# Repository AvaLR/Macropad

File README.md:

# Macropad

PCB:
- Started to design this in KiCad starting with the skematic design and then moving to the PCB design.
- I originally started with a 3X4 with 2 rotary encoders and 1 OLED
- I wanted to add LEDs so I removed 1 rotary encoder and made the other rotary encoder's button the same as button 3. Also made it a 3X3 instead of a 3X4.
- Wiring was a challenge and reminded me of that Flow Free game so it was kinda fun in that aspect.

Enclosure:
- A lot easier then the PCB
- First I inserted a .step file of my PCB into AutoDesk Fusion 
- Then based on the PCB I made my bottom enclosure (120mm X 100mm X 13mm) with 2.9mm holes in each corner so I can add screws to put my top and bottom enclosures together. I also put a hole on back for the USB.
- After I made the bottom enclosure I created the top enclosure with holes for all my buttons (inserting my PCB design really helped for this part because I knew exactly where the holes went). I put 2.9mm holes here as well to again be able to put the top and bottom together. 
- The top enclosure was a 120mm x 100mm x 3mm so with the top and bottom enclosure together it turned into a 120mm x 100mm x 16mm enclosure.

Firmware:
- Created 3 layers of Buttons: Daily, AVTF & Coding
- Each layer does different things that will make my life easier from study time to coding to editing videos!
- Each layer has its own RGB unkeyglow color, and the OLED will show what the layer I'm on

Credit: 
- Info & Guide - Hack Club
- PCB, Enclosure, Firmware - Ava Russell using QMK Resources/Code/Guide
- Debugging Help - AI

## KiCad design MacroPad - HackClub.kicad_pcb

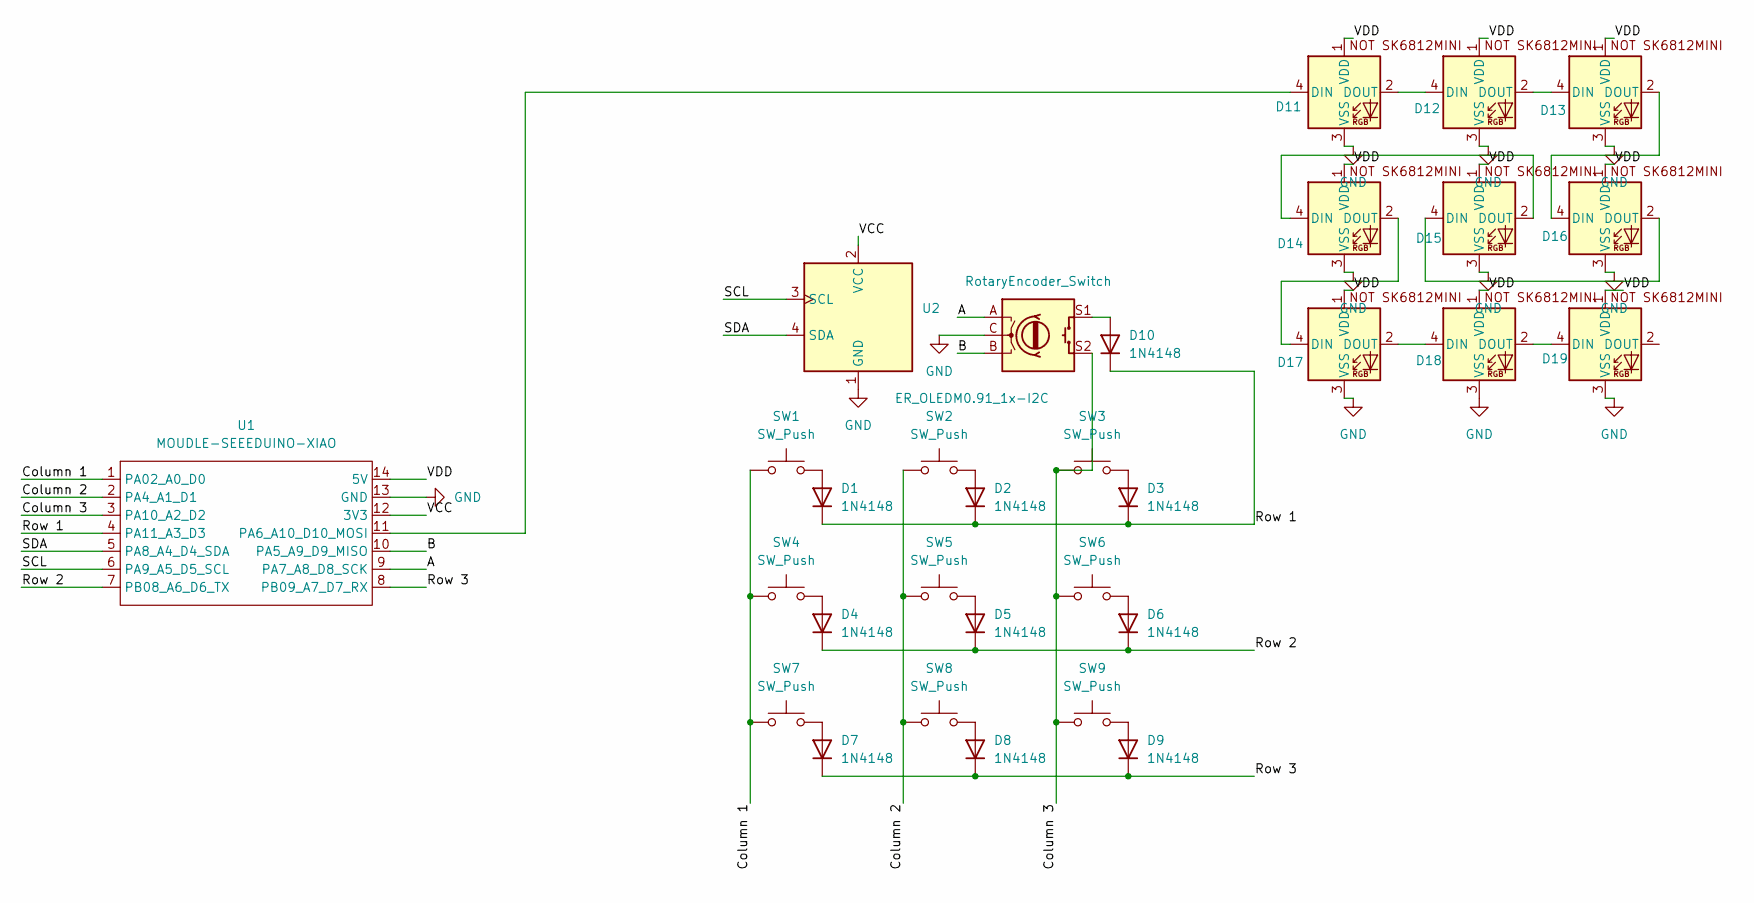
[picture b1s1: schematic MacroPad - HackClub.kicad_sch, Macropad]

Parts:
D1, D2, D3, D4, D5, D6, D7, D8, D9, D10: 1N4148; D_DO-35_SOD27_P7.62mm_Horizontal
D11, D12, D13, D14, D15, D16, D17, D18, D19: SK6812MINI-E; SK6812MINI-E_fixed
SW1, SW2, SW3, SW4, SW5, SW6, SW7, SW8, SW9: SW_Push; SW_Cherry_MX_1.00u_PCB
SW10: RotaryEncoder_Switch; RotaryEncoder_Alps_EC11E-Switch_Vertical_H20mm
U1: MOUDLE-SEEEDUINO-XIAO; XIAO-Generic-Hybrid-14P-2.54-21X17.8MM
U2: ER_OLEDM0.91_1x-I2C

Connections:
/A: SW10.A, U1.9 (PA7_A8_D8_SCK)
/B: SW10.B, U1.10 (PA5_A9_D9_MISO)
/Column 1: SW1.1, SW4.1, SW7.1, U1.1 (PA02_A0_D0)
/Column 2: SW2.1, SW5.1, SW8.1, U1.2 (PA4_A1_D1)
/Column 3: SW3.1, SW6.1, SW9.1, SW10.S2, U1.3 (PA10_A2_D2)
/Row 1: D1.1 (K), D2.1 (K), D3.1 (K), D10.1 (K), U1.4 (PA11_A3_D3)
/Row 2: D4.1 (K), D5.1 (K), D6.1 (K), U1.7 (PB08_A6_D6_TX)
/Row 3: D7.1 (K), D8.1 (K), D9.1 (K), U1.8 (PB09_A7_D7_RX)
/SCL: U1.6 (PA9_A5_D5_SCL), U2.3 (SCL)
/SDA: U1.5 (PA8_A4_D4_SDA), U2.4 (SDA)
/VCC: U1.12 (3V3), U2.2 (VCC)
/VDD: D11.1 (VDD), D12.1 (VDD), D13.1 (VDD), D14.1 (VDD), D15.1 (VDD), D16.1 (VDD), D17.1 (VDD), D18.1 (VDD), D19.1 (VDD), U1.14 (5V)
GND: D11.3 (VSS), D12.3 (VSS), D13.3 (VSS), D14.3 (VSS), D15.3 (VSS), D16.3 (VSS), D17.3 (VSS), D18.3 (VSS), D19.3 (VSS), SW10.C, U1.13 (GND), U2.1 (GND)
unnamed: D1.2 (A), SW1.2
unnamed: D2.2 (A), SW2.2
unnamed: D3.2 (A), SW3.2
unnamed: D4.2 (A), SW4.2
unnamed: D5.2 (A), SW5.2
unnamed: D6.2 (A), SW6.2
unnamed: D7.2 (A), SW7.2
unnamed: D8.2 (A), SW8.2
unnamed: D9.2 (A), SW9.2
unnamed: D10.2 (A), SW10.S1
unnamed: D11.4 (DIN), U1.11 (PA6_A10_D10_MOSI)
unnamed: D11.2 (DOUT), D12.4 (DIN)
unnamed: D12.2 (DOUT), D13.4 (DIN)
unnamed: D13.2 (DOUT), D16.4 (DIN)
unnamed: D14.4 (DIN), D15.2 (DOUT)
unnamed: D14.2 (DOUT), D17.4 (DIN)
unnamed: D15.4 (DIN), D16.2 (DOUT)
unnamed: D17.2 (DOUT), D18.4 (DIN)
unnamed: D18.2 (DOUT), D19.4 (DIN)

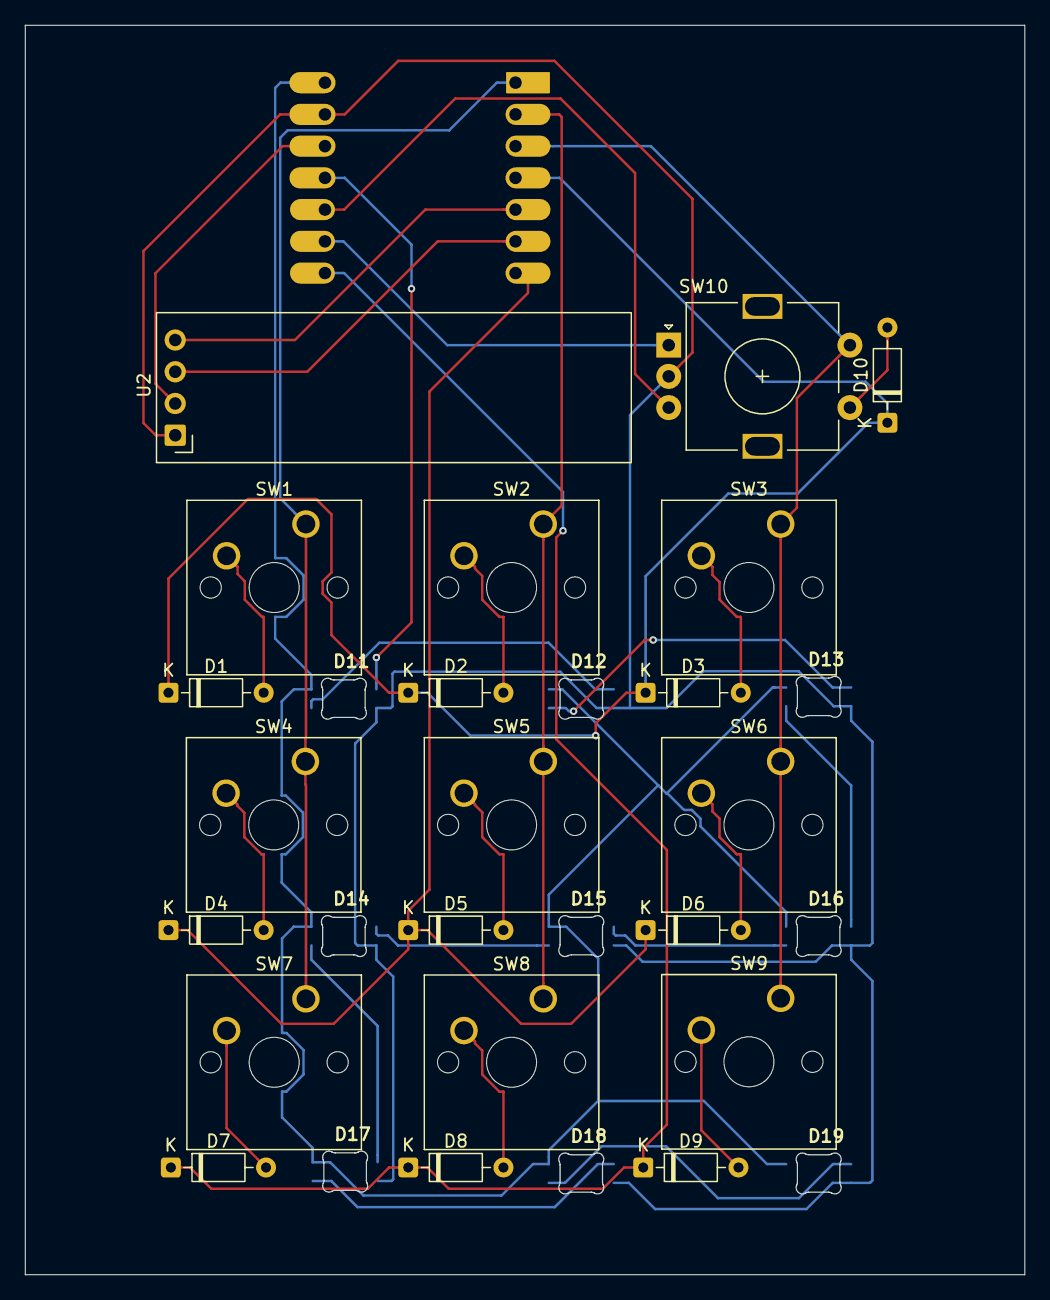
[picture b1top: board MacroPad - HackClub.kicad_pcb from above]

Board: 2 copper layers, 80.0 x 100.0 mm, 31 parts (1 on the bottom side), 32 nets.
